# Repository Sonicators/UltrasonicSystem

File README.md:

A small ultrasonic system which can be used by hobbyists for:

* Mixing
* Cell disruption
* Levitation
* Cavitation experiments
* Ultrasonic chemistry
* ...and other tasks

The system consists of a transducer, a tuned aluminum horn, an ATX supply for power, an SMPS transformer from a second power supply, a PCB power driver, and mounting hardware.

Not counting the two ATX power supplies, a complete system can be made for around $60USD, more or less, depending on how good you are at scavenging.

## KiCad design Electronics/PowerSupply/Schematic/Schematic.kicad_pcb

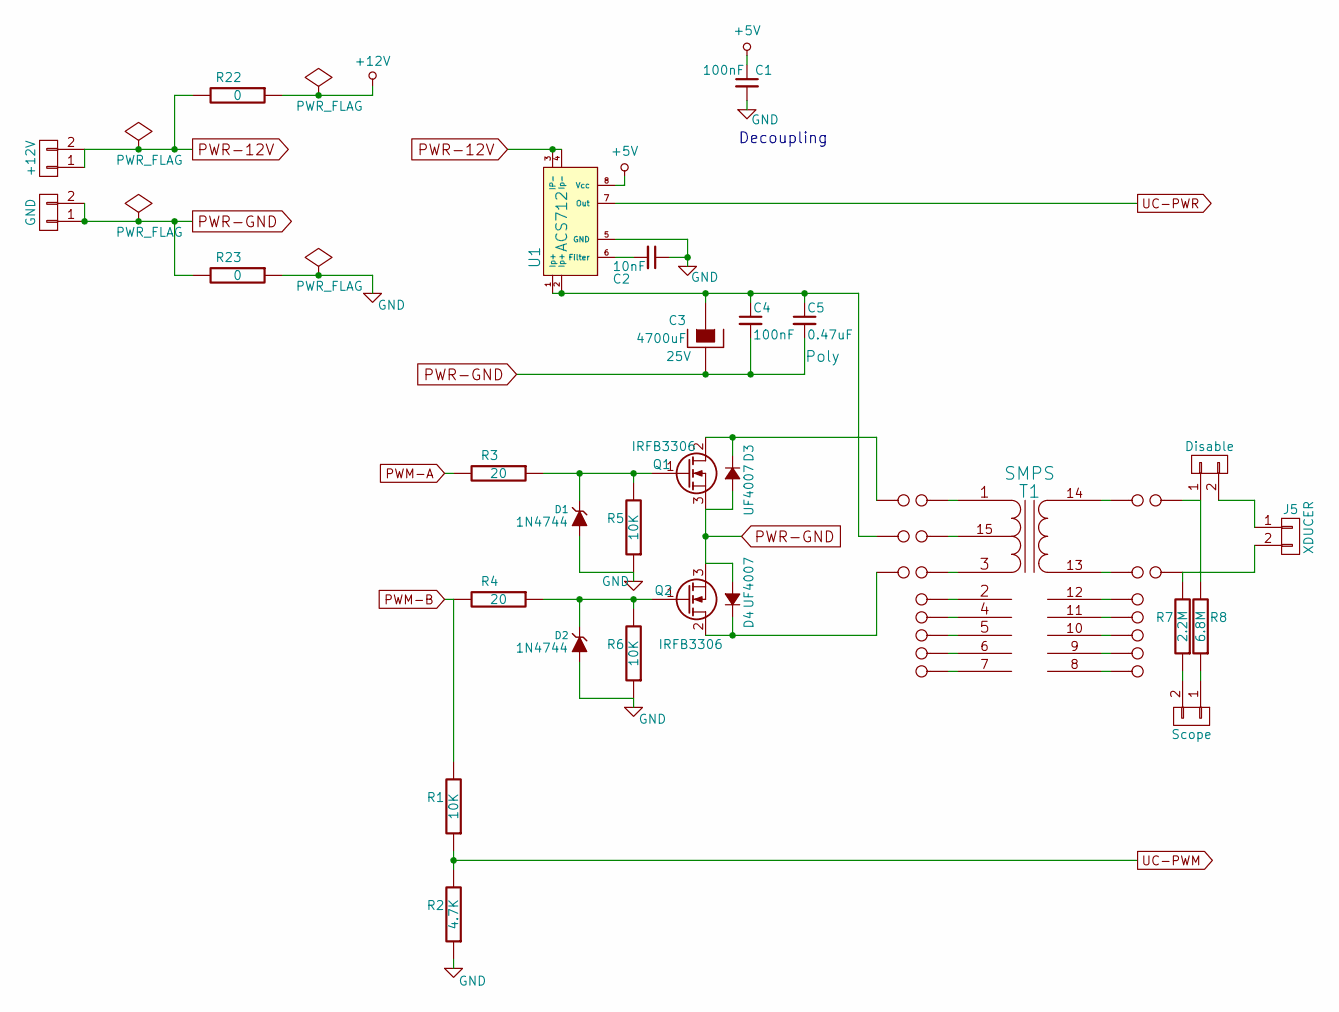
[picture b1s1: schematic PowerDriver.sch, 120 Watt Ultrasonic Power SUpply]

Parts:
C1, C4: 100nF; C_0805_HandSoldering
C2: 10nF; C_0805_HandSoldering
C3: 4700uF; C_Radial_D18_L36_P7.5; Voltage 25V
C5: 0.47uF; C_Rect_L18_W9_H15_P15
D1, D2: 1N4744; Diode_DO-41_SOD81_Horizontal_RM10
D3, D4: UF4007; Diode_DO-41_SOD81_Horizontal_RM10
J1: +12V; AK300-2
J2: GND; AK300-2
J3: Scope; PINHEAD1-2
J4: Disable; AK300-2
J5: XDUCER; AK300-2
P7: SMPS-UT; 1pin
P8: SMPS-CT; 1pin
P9: SMPS-LT; 1pin
P10, P11, P12, P13, P14, P15, P16, P17, P18, P19, P20, P21, P22, P23, P24, P25, P26: CONN_1; 1pin
Q1, Q2: IRFB3306; TO-220_Neutral123_Horizontal_LargePads
R1, R5, R6: 10K; R_0805_HandSoldering
R2: 4.7K; R_0805_HandSoldering
R3, R4: 20; R_0805_HandSoldering
R7: 2.2M; R_0805_HandSoldering
R8: 6.8M; R_0805_HandSoldering
R22, R23: 0; TEST_POINT_2PADS
T1: SMPS; SMPS_Transformer
U1: ACS712; SOIC-8-N

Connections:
+5V: C1.1, U1.8 (Vcc); also elsewhere on the board
+12V: R22.1; also elsewhere on the board
GND: C1.2, C2.1, D1.1 (A), D2.1 (A), R2.1, R5.1, R6.1, R23.1, U1.5 (GND); also elsewhere on the board
unnamed: C2.2, U1.6 (Filter)
unnamed: C3.1, C4.1, C5.1, P8.1, U1.1 (Ip+), U1.2 (Ip+)
unnamed: D1.2 (K), Q1.1 (G), R3.1, R5.2
unnamed: D2.2 (K), Q2.1 (G), R4.1, R6.2
unnamed: D3.2 (C), P7.1, Q1.2 (D)
unnamed: D4.2 (C), P9.1, Q2.2 (D)
unnamed: J3.1, R8.1
unnamed: J3.2, R7.1
unnamed: J4.1, P25.1, R8.2
unnamed: J4.2, J5.1
unnamed: J5.2, P26.1, R7.2
unnamed: P10.1, T1.1 (PR1)
unnamed: P11.1, T1.15 (TAIL)
unnamed: P12.1, T1.3 (PR2)
unnamed: P13.1, T1.2 (PM)
unnamed: P14.1, T1.4 (S1)
unnamed: P15.1, T1.5 (S2)
unnamed: P16.1, T1.6
unnamed: P17.1, T1.7
unnamed: P18.1, T1.14
unnamed: P19.1, T1.13
unnamed: P20.1, T1.12
unnamed: P21.1, T1.11
unnamed: P22.1, T1.10
unnamed: P23.1, T1.9
unnamed: P24.1, T1.8
PWM-A: R3.2; also elsewhere on the board
PWM-B: R1.2, R4.2; also elsewhere on the board
PWR-12V: J1.1, J1.2, R22.2, U1.3 (IP-), U1.4 (Ip-)
PWR-GND: C3.2, C4.2, C5.2, D3.1 (A), D4.1 (A), J2.1, J2.2, Q1.3 (S), Q2.3 (S), R23.2
UC-PWM: R1.1, R2.2; also elsewhere on the board
UC-PWR: U1.7 (Out); also elsewhere on the board

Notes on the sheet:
Decoupling

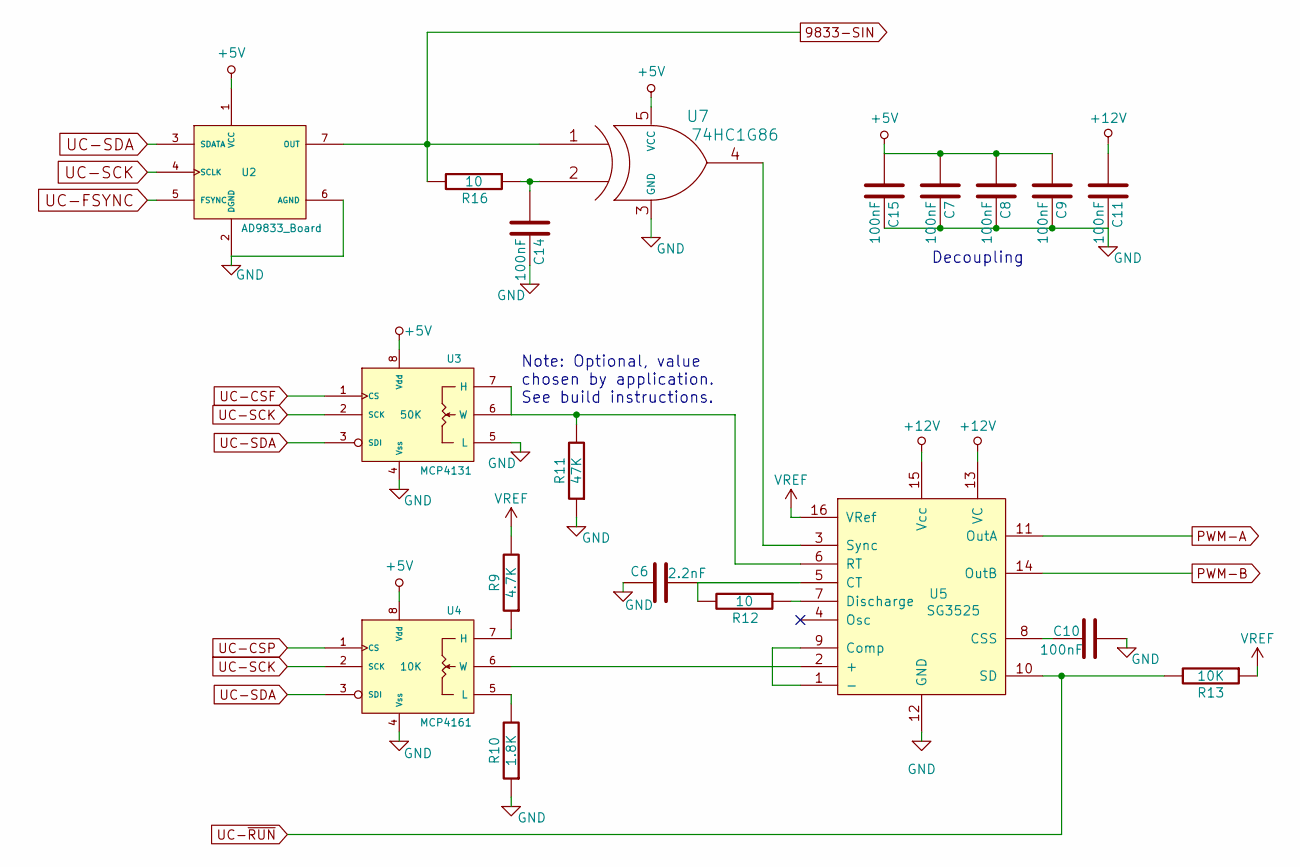
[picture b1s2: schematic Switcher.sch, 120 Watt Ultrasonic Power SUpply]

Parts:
C6: 2.2nF; C_0603_HandSoldering
C7, C8, C9, C10, C11, C14, C15: 100nF; C_0805_HandSoldering
R9: 4.7K; R_0805_HandSoldering
R10: 1.8K; R_0805_HandSoldering
R11: 47K; PINHEAD1-2
R12, R16: 10; R_0805_HandSoldering
R13: 10K; R_0805_HandSoldering
U2: AD9833_Board
U3: 50K; DIP-8_W7.62mm_LongPads
U4: 10K; DIP-8_W7.62mm_LongPads
U5: SG3525; DIP-16_W7.62mm_LongPads
U7: 74HC1G86; SOT-23-5

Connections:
9833-SIN: R16.2, U2.7 (OUT), U7.1; also elsewhere on the board
+5V: C7.2, C8.2, C9.2, C15.2, U2.1 (VCC), U3.8 (Vdd), U4.8 (Vdd), U7.5 (VCC); also elsewhere on the board
+12V: C11.2, U5.13 (VC), U5.15 (Vcc); also elsewhere on the board
GND: C6.1, C7.1, C8.1, C9.1, C10.1, C11.1, C14.1, C15.1, R10.1, R11.1, U2.2 (DGND), U2.6 (AGND), U3.4 (Vss), U3.5 (L), U4.4 (Vss), U5.12 (GND), U7.3 (GND); also elsewhere on the board
unnamed: C6.2, R12.2, U5.5 (CT)
unnamed: C10.2, U5.8 (CSS)
unnamed: C14.2, R16.1, U7.2
unnamed: R9.1, U4.7 (H)
unnamed: R10.2, U4.5 (L)
unnamed: R11.2, U3.6 (W), U3.7 (H), U5.6 (RT)
unnamed: R12.1, U5.7 (Discharge)
unnamed: U4.6 (W), U5.2 (+)
unnamed: U5.1 (-), U5.9 (Comp)
unnamed: U5.3 (Sync), U7.4
PWM-A: U5.11 (OutA); also elsewhere on the board
PWM-B: U5.14 (OutB); also elsewhere on the board
UC-CSF: U3.1 (CS); also elsewhere on the board
UC-CSP: U4.1 (CS); also elsewhere on the board
UC-FSYNC: U2.5 (FSYNC); also elsewhere on the board
UC-SCK: U2.4 (SCLK), U3.2 (SCK), U4.2 (SCK); also elsewhere on the board
UC-SDA: U2.3 (SDATA), U3.3 (SDI), U4.3 (SDI); also elsewhere on the board
UC-~RUN: R13.2, U5.10 (SD); also elsewhere on the board
VREF: R9.2, R13.1, U5.16 (VRef)

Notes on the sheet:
Decoupling
Note: Optional, value chosen by application. See build instructions.

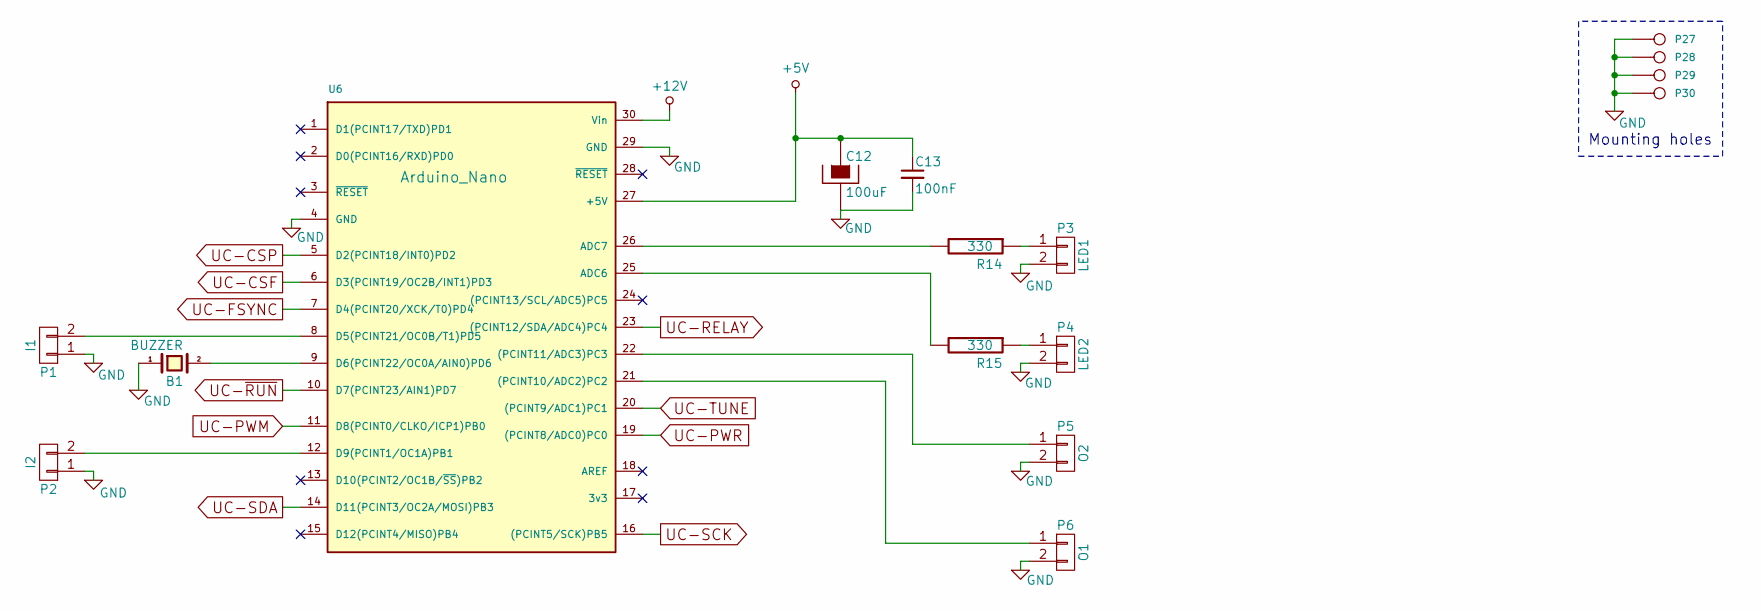
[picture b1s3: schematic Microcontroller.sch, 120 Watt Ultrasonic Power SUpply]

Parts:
B1: BUZZER; BUZ3-5
C12: 100uF; c_elec_8x6.7
C13: 100nF; C_0805_HandSoldering
P1: I1; PINHEAD1-2
P2: I2; PINHEAD1-2
P3: LED1; PINHEAD1-2
P4: LED2; PINHEAD1-2
P5: O2; PINHEAD1-2
P6: O1; PINHEAD1-2
P27, P28, P29, P30: CONN_1; 1pin
R14, R15: 330; R_0805_HandSoldering
U6: Arduino_Nano; DIP-30_W15.24mm_LongPads

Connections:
+5V: C12.1, C13.1, U6.27 (+5V); also elsewhere on the board
+12V: U6.30 (Vin); also elsewhere on the board
GND: B1.1, C12.2, C13.2, P1.1, P2.1, P3.2, P4.2, P5.2, P6.2, P27.1, P28.1, P29.1, P30.1, U6.4 (GND), U6.29 (GND); also elsewhere on the board
unnamed: B1.2, U6.9 (D6(PCINT22/OC0A/AIN0)PD6)
unnamed: P1.2, U6.8 (D5(PCINT21/OC0B/T1)PD5)
unnamed: P2.2, U6.12 (D9(PCINT1/OC1A)PB1)
unnamed: P3.1, R14.1
unnamed: P4.1, R15.1
unnamed: P5.1, U6.22 ((PCINT11/ADC3)PC3)
unnamed: P6.1, U6.21 ((PCINT10/ADC2)PC2)
unnamed: R14.2, U6.26 (ADC7)
unnamed: R15.2, U6.25 (ADC6)
UC-CSF: U6.6 (D3(PCINT19/OC2B/INT1)PD3); also elsewhere on the board
UC-CSP: U6.5 (D2(PCINT18/INT0)PD2); also elsewhere on the board
UC-FSYNC: U6.7 (D4(PCINT20/XCK/T0)PD4); also elsewhere on the board
UC-PWM: U6.11 (D8(PCINT0/CLKO/ICP1)PB0); also elsewhere on the board
UC-PWR: U6.19 ((PCINT8/ADC0)PC0); also elsewhere on the board
UC-RELAY: U6.23 ((PCINT12/SDA/ADC4)PC4); also elsewhere on the board
UC-SCK: U6.16 ((PCINT5/SCK)PB5); also elsewhere on the board
UC-SDA: U6.14 (D11(PCINT3/OC2A/MOSI)PB3); also elsewhere on the board
UC-TUNE: U6.20 ((PCINT9/ADC1)PC1); also elsewhere on the board
UC-~RUN: U6.10 (D7(PCINT23/AIN1)PD7); also elsewhere on the board

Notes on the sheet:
Mounting holes

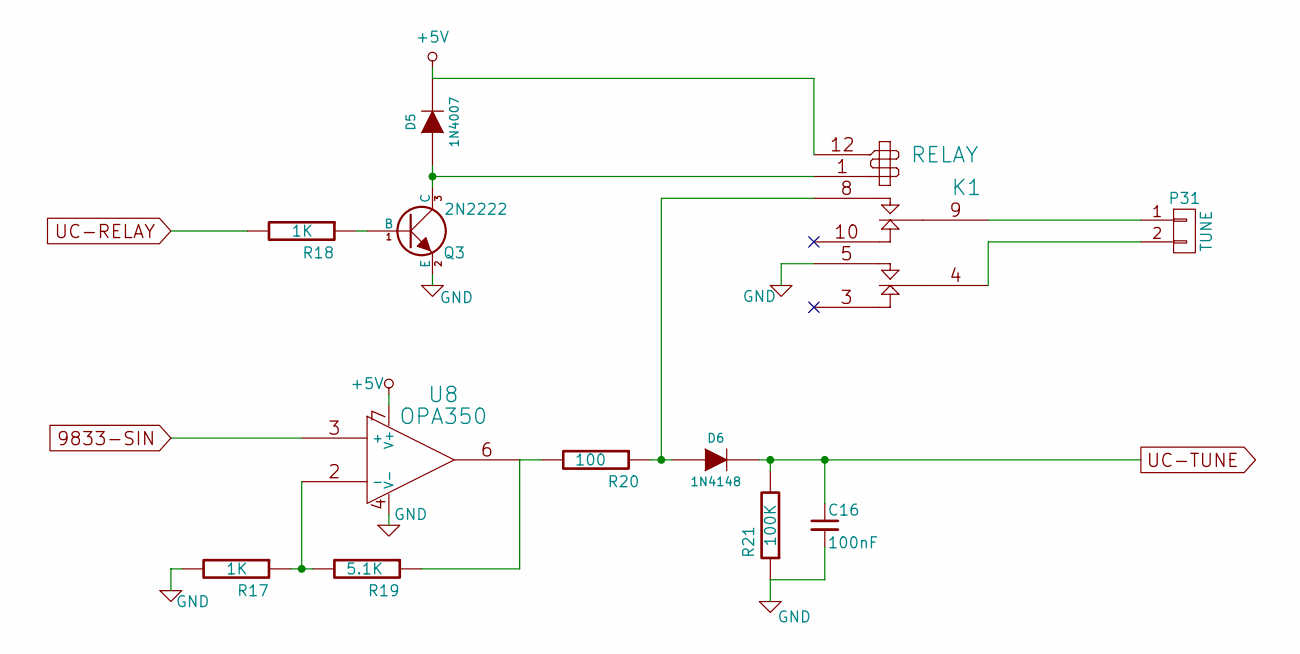
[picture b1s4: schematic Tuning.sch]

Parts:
C16: 100nF; C_0805_HandSoldering
D5: 1N4007; Diode_DO-41_SOD81_Horizontal_RM10
D6: 1N4148; Diode_DO-41_SOD81_Horizontal_RM10
K1: RELAY; Relay_DPDT_IM0(3,6,7)NS
P31: TUNE; PINHEAD1-2
Q3: 2N2222; SOT-23_Handsoldering
R17, R18: 1K; R_0805_HandSoldering
R19: 5.1K; R_0805_HandSoldering
R20: 100; R_0805_HandSoldering
R21: 100K; R_0805_HandSoldering
U8: OPA350; SOIC-8-N

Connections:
9833-SIN: U8.3 (+); also elsewhere on the board
+5V: D5.2 (K), K1.12, U8.7 (V+); also elsewhere on the board
GND: C16.2, K1.5 (T2), Q3.2 (E), R17.2, R21.1, U8.4 (V-); also elsewhere on the board
unnamed: D5.1 (A), K1.1, Q3.3 (C)
unnamed: D6.1 (A), K1.8 (T1), R20.1
unnamed: K1.4 (C2), P31.2
unnamed: K1.9 (C1), P31.1
unnamed: Q3.1 (B), R18.1
unnamed: R17.1, R19.2, U8.2 (-)
unnamed: R19.1, R20.2, U8.6
UC-RELAY: R18.2; also elsewhere on the board
UC-TUNE: C16.1, D6.2 (K), R21.2; also elsewhere on the board

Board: 2 copper layers, 95 parts (8 on the bottom side), 71 nets, no tracks yet.

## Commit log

2015-09-23 Completed Board layout and generated gerber files.
2015-09-23 Completed board layout, generated gerber files
2016-09-05 Added resonance finder for offline request
